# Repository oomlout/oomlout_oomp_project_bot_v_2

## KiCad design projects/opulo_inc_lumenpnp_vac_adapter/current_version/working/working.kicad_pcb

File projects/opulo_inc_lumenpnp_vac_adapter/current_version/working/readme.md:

# lumenpnp
 
## summary 
* id: opulo_inc_lumenpnp_vac_adapter
* user: opulo_inc
* name: lumenpnp
* board: vac_adapter
* repo: https://github.com/opulo-inc/lumenpnp
* src_file_repo_kicad_pcb: pnp/pcb/vac-interposer/vac-adapter.kicad_pcb
* src_file_repo_kicad_pcb_link: https://github.com/opulo-inc/lumenpnp/tree/main/pnp/pcb/vac-interposer/vac-adapter.kicad_pcb
* src_file_repo_kicad_sch: pnp/pcb/vac-interposer/vac-adapter.kicad_sch
* src_file_repo_kicad_sch_link: https://github.com/opulo-inc/lumenpnp/tree/main/pnp/pcb/vac-interposer/vac-adapter.kicad_sch

* src_file_repo_sch: 
* src_file_repo_sch_link: https://github.com/opulo-inc/lumenpnp/tree/main/
* full details link: https://github.com/oomlout/oomlout_oomp_project_bot_v_2/tree/main/projects/opulo_inc_lumenpnp_vac_adapter/current_version/working

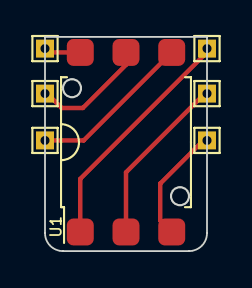
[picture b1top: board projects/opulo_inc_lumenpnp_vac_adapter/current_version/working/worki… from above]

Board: 2 copper layers, 9.0 x 11.9 mm, 7 parts (0 on the bottom side), 6 nets.

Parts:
TP1, TP2, TP3, TP4, TP5, TP6: TestPoint; TestPoint_THTPad_1.0x1.0mm_Drill0.5mm
U1: XGZP; SO-6_7x7mm_P2.54mm

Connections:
unnamed: TP1.1, U1.6 (Vo-)
unnamed: TP2.1, U1.4 (N/C)
unnamed: TP3.1, U1.5 (GND)
unnamed: TP4.1, U1.1 (Vo-)
unnamed: TP5.1, U1.2 (Vs+)
unnamed: TP6.1, U1.3 (Vo+)

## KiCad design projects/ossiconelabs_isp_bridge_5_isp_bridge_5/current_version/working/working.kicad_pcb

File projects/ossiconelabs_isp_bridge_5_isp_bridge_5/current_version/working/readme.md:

# isp_bridge_5
 
## summary 
* id: ossiconelabs_isp_bridge_5_isp_bridge_5
* user: ossiconelabs
* name: isp_bridge_5
* board: isp_bridge_5
* repo: https://github.com/OssiconeLabs/ISP-Bridge-5
* src_file_repo_kicad_pcb: ISP-Bridge-5.kicad_pcb
* src_file_repo_kicad_pcb_link: https://github.com/OssiconeLabs/ISP-Bridge-5/tree/master/ISP-Bridge-5.kicad_pcb

* src_file_repo_sch: ISP-Bridge-5.sch
* src_file_repo_sch_link: https://github.com/OssiconeLabs/ISP-Bridge-5/tree/master/ISP-Bridge-5.sch
* full details link: https://github.com/oomlout/oomlout_oomp_project_bot_v_2/tree/main/projects/ossiconelabs_isp_bridge_5_isp_bridge_5/current_version/working

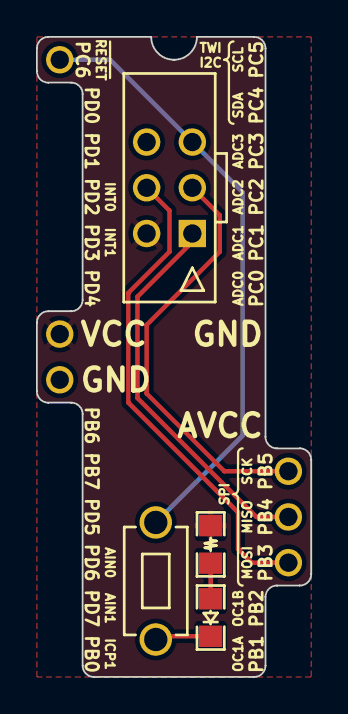
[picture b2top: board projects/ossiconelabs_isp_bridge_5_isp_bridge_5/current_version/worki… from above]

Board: 2 copper layers, 15.2 x 35.6 mm, 6 parts (0 on the bottom side), 7 nets.

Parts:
D1: LED; LED_0805_Symbol
IC1: ATMEGA328-P; Atmel_ATtiny-x8_ATmega-x8
J1: ATMEL_ISP_6PIN; Atmel_ISP_6PIN
R1: 1K; R_0805_Symbol
SW1: SW_PUSH; SW_PUSH_MJTP1250
VAL: REF; Ossicone_Labs_Logo_0.165prop_flipped

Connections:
GND: D1.1, IC1.8, J1.6, SW1.1
unnamed: D1.2, R1.2
unnamed: IC1.1, J1.5, SW1.2
unnamed: IC1.17, J1.4
unnamed: IC1.18, J1.1
unnamed: IC1.19, J1.3
VCC: IC1.7, J1.2, R1.1

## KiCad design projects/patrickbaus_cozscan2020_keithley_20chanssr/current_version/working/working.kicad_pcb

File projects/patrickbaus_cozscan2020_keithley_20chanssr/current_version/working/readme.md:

# cozscan2020
 
## summary 
* id: patrickbaus_cozscan2020_keithley_20chanssr
* user: patrickbaus
* name: cozscan2020
* board: keithley_20chanssr
* repo: https://github.com/PatrickBaus/CozScan2020
* src_file_repo_kicad_pcb: KiCad/Keithley_20ChanSSR/Keithley_20ChanSSR.kicad_pcb
* src_file_repo_kicad_pcb_link: https://github.com/PatrickBaus/CozScan2020/tree/master/KiCad/Keithley_20ChanSSR/Keithley_20ChanSSR.kicad_pcb

* src_file_repo_sch: KiCad/Keithley_20ChanSSR/Keithley_20ChanSSR.sch
* src_file_repo_sch_link: https://github.com/PatrickBaus/CozScan2020/tree/master/KiCad/Keithley_20ChanSSR/Keithley_20ChanSSR.sch
* full details link: https://github.com/oomlout/oomlout_oomp_project_bot_v_2/tree/main/projects/patrickbaus_cozscan2020_keithley_20chanssr/current_version/working

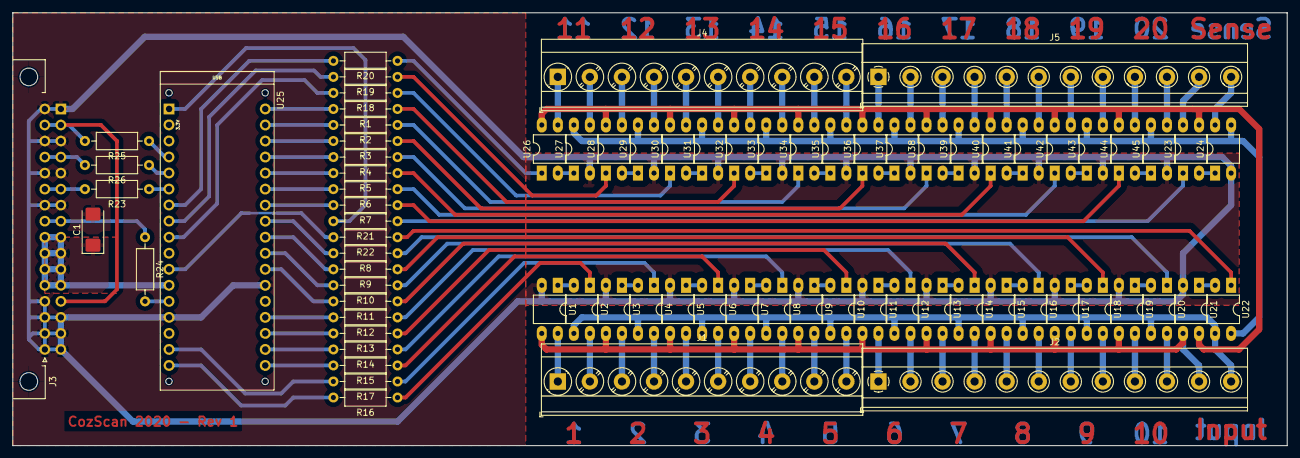
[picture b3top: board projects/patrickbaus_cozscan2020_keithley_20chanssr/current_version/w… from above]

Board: 2 copper layers, 201.9 x 68.6 mm, 77 parts (0 on the bottom side), 122 nets.

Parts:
C1: 10u; CP_EIA-6032-20_AVX-F
J1, J4: Screw_Terminal_01x10; TerminalBlock_Phoenix_MKDS-3-10-5.08_1x10_P5.08mm_Horizontal
J2, J5: Screw_Terminal_01x12; TerminalBlock_Phoenix_MKDS-1,5-12-5.08_1x12_P5.08mm_Horizon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
J3: Conn_02x16_Top_Bottom; DIN41612_B2_2x16_Horizontal
R1, R2, R3, R4, R5, R6, R7, R8, R9, R10, R11, R12, R13, R14, R15, R16, R17, R18, R19, R20, R21, R22, R23, R24, R25, R26: R; R_Axial_DIN0207_L6.3mm_D2.5mm_P10.16mm_Horizontal
U1, U2, U3, U4, U5, U6, U7, U8, U9, U10, U11, U12, U13, U14, U15, U16, U17, U18, U19, U20, U21, U22, U23, U24, U26, U27, U28, U29, U30, U31, U32, U33, U34, U35, U36, U37, U38, U39, U40, U41, U42, U43, U44, U45: TLP3558; DIP-4_W7.62mm_LongPads_coz
U25: Arduino_Micro; Arduino_Micro_Socket_coz

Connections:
+5V: C1.1, J3.9, J3.10, J3.11, J3.12, J3.25, J3.26, J3.27, J3.28, U25.12
/SENSE_LO: J5.11, U23.4
BUSB_2_INPUT: R22.1, U22.1
BUSB_2_SENSE: R21.1, U23.1
CH1: R16.1, U2.1
CH2: R17.1, U4.1
CH3: R15.1, U6.1
CH4: R14.1, U8.1
CH5: R13.1, U10.1
CH6: R12.1, U12.1
CH7: R11.1, U14.1
CH8: R10.1, U16.1
CH9: R9.1, U18.1
CH10: R8.1, U20.1
CH11: R20.1, U26.1
CH12: R19.1, U28.1
CH13: R18.1, U30.1
CH14: R1.1, U32.1
CH15: R2.1, U34.1
CH16: R3.1, U36.1
CH17: R4.1, U38.1
CH18: R5.1, U40.1
CH19: R6.1, U42.1
CH20: R7.1, U44.1
CLK: J3.4, J3.20, R26.2
DATA: J3.2, J3.13, J3.18, R25.2
GND: C1.2, J3.1, J3.3, J3.5, J3.7, J3.14, J3.15, J3.16, J3.17, J3.19, J3.21, J3.23, J3.29, J3.30, J3.31, J3.32, U1.2, U3.2, U5.2, U7.2, U9.2, U11.2, U13.2, U15.2, U17.2, U19.2, U21.2, U24.2, U25.14, U25.23, U27.2, U29.2, U31.2, U33.2, U35.2, U37.2, U39.2, U41.2, U43.2, U45.2
unnamed: J1.1, U1.4
unnamed: J1.2, U2.4
unnamed: J1.3, U3.4
unnamed: J1.4, U4.4
unnamed: J1.5, U5.4
unnamed: J1.6, U6.4
unnamed: J1.7, U7.4
unnamed: J1.8, U8.4
unnamed: J1.9, U9.4
unnamed: J1.10, U10.4
unnamed: J2.1, U11.4
unnamed: J2.2, U12.4
unnamed: J2.3, U13.4
unnamed: J2.4, U14.4
unnamed: J2.5, U15.4
unnamed: J2.6, U16.4
unnamed: J2.7, U17.4
unnamed: J2.8, U18.4
unnamed: J2.9, U19.4
unnamed: J2.10, U20.4
unnamed: J2.11, U1.3, U3.3, U5.3, U7.3, U9.3, U11.3, U13.3, U15.3, U17.3, U19.3, U21.3
unnamed: J2.12, U2.3, U4.3, U6.3, U8.3, U10.3, U12.3, U14.3, U16.3, U18.3, U20.3, U22.3
unnamed: J4.1, U26.3
unnamed: J4.2, U27.3
unnamed: J4.3, U28.3
unnamed: J4.4, U29.3
unnamed: J4.5, U30.3
unnamed: J4.6, U31.3
unnamed: J4.7, U32.3
unnamed: J4.8, U33.3
unnamed: J4.9, U34.3
unnamed: J4.10, U35.3
unnamed: J5.1, U36.3
unnamed: J5.2, U37.3
unnamed: J5.3, U38.3
unnamed: J5.4, U39.3
unnamed: J5.5, U40.3
unnamed: J5.6, U41.3
unnamed: J5.7, U42.3
unnamed: J5.8, U43.3
unnamed: J5.9, U44.3
unnamed: J5.10, U45.3
unnamed: J5.12, U24.4
unnamed: R1.2, U25.34
unnamed: R2.2, U25.33
unnamed: R3.2, U25.32
unnamed: R4.2, U25.31
unnamed: R5.2, U25.30
unnamed: R6.2, U25.29
unnamed: R7.2, U25.28
unnamed: R8.2, U25.27
unnamed: R9.2, U25.26
unnamed: R10.2, U25.25
unnamed: R11.2, U25.24
unnamed: R12.2, U25.21
unnamed: R13.2, U25.20
unnamed: R14.2, U25.19
unnamed: R15.2, U25.18
unnamed: R16.2, U25.17
unnamed: R17.2, U25.16
unnamed: R18.2, U25.9
unnamed: R19.2, U25.8
unnamed: R20.2, U25.7
unnamed: R21.2, U25.1
unnamed: R22.2, U25.11
unnamed: R23.1, U25.6
unnamed: R24.2, U25.13
unnamed: R25.1, U25.4
unnamed: R26.1, U25.5
unnamed: U1.1, U2.2
unnamed: U3.1, U4.2
unnamed: U5.1, U6.2
unnamed: U7.1, U8.2
unnamed: U9.1, U10.2
unnamed: U11.1, U12.2
unnamed: U13.1, U14.2
unnamed: U15.1, U16.2
unnamed: U17.1, U18.2
unnamed: U19.1, U20.2
unnamed: U21.1, U22.2
unnamed: U21.4, U23.3, U26.4, U28.4, U30.4, U32.4, U34.4, U36.4, U38.4, U40.4, U42.4, U44.4
unnamed: U22.4, U24.3, U27.4, U29.4, U31.4, U33.4, U35.4, U37.4, U39.4, U41.4, U43.4, U45.4
unnamed: U23.2, U24.1
unnamed: U26.2, U27.1
unnamed: U28.2, U29.1
unnamed: U30.2, U31.1
unnamed: U32.2, U33.1
unnamed: U34.2, U35.1
unnamed: U36.2, U37.1
unnamed: U38.2, U39.1
unnamed: U40.2, U41.1
unnamed: U42.2, U43.1
unnamed: U44.2, U45.1
RESET: J3.8, J3.24, R24.1
STROBE: J3.6, J3.22, R23.2

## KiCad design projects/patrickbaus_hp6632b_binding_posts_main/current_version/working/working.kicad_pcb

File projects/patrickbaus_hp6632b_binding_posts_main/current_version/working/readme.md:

# hp6632b_binding_posts
 
## summary 
* id: patrickbaus_hp6632b_binding_posts_main
* user: patrickbaus
* name: hp6632b_binding_posts
* board: main
* repo: https://github.com/PatrickBaus/HP6632B_binding_posts
* src_file_repo_kicad_pcb: main.kicad_pcb
* src_file_repo_kicad_pcb_link: https://github.com/PatrickBaus/HP6632B_binding_posts/tree/master/main.kicad_pcb

* src_file_repo_sch: main.sch
* src_file_repo_sch_link: https://github.com/PatrickBaus/HP6632B_binding_posts/tree/master/main.sch
* full details link: https://github.com/oomlout/oomlout_oomp_project_bot_v_2/tree/main/projects/patrickbaus_hp6632b_binding_posts_main/current_version/working

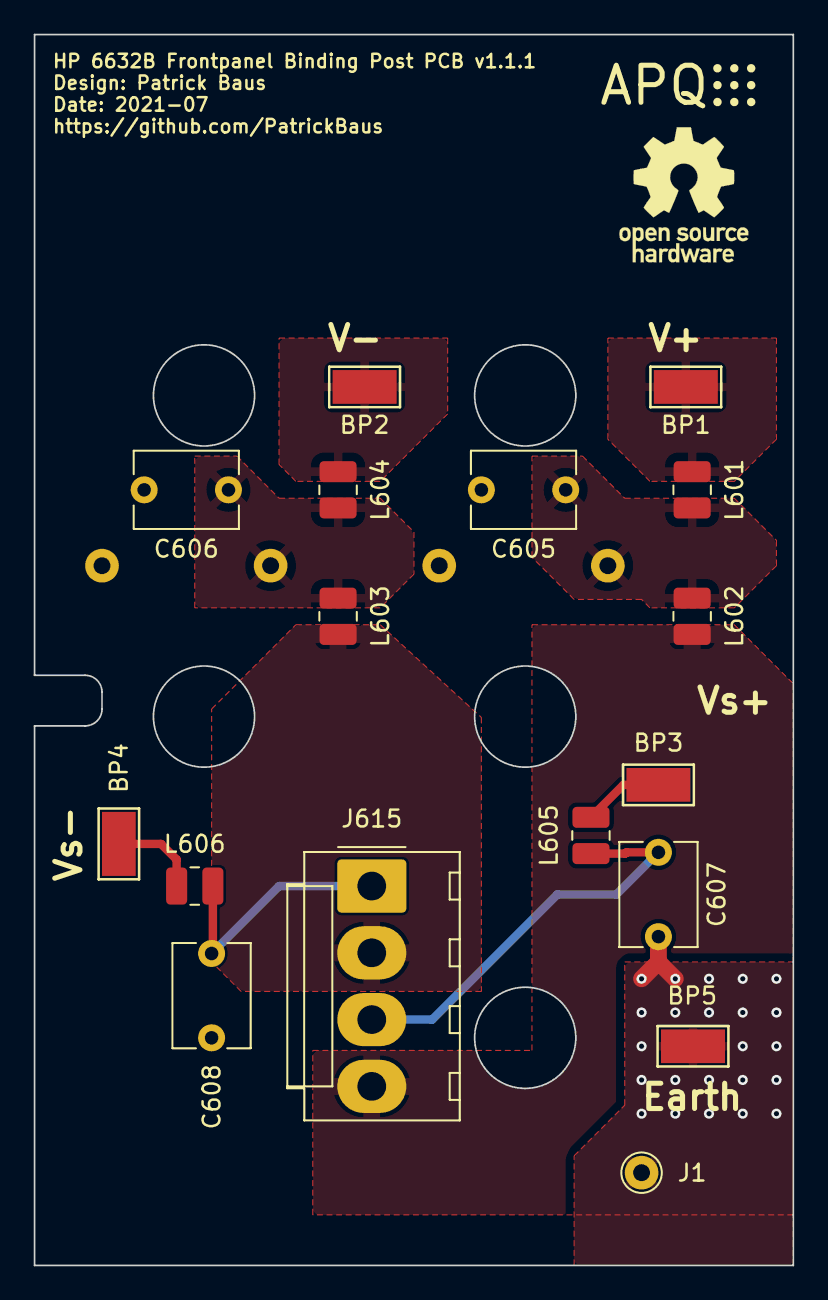
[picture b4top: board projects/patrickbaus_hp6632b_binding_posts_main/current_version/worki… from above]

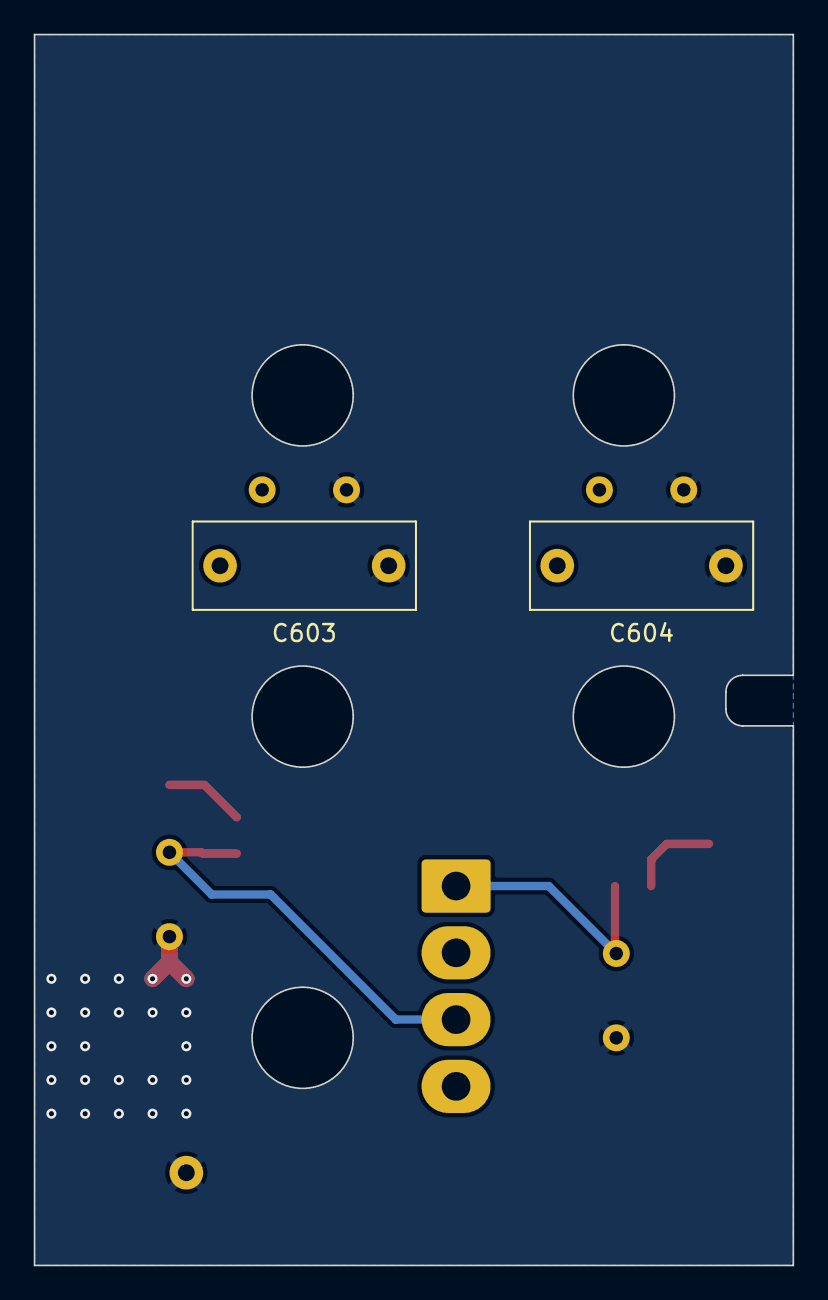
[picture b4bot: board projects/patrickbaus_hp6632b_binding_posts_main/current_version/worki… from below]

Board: 2 copper layers, 45.0 x 73.0 mm, 21 parts (2 on the bottom side), 11 nets.

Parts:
BP1, BP2, BP3, BP4, BP5: Conn_01x01; TestPoint_Keystone_5019_Minature
C603, C604: 4.7n; C_Rect_L13.0mm_W5.0mm_P10.00mm_FKS3_FKP3_MKS4
C605, C606, C607, C608: 220p; C_Disc_D6.0mm_W4.4mm_P5.00mm
J1: Conn_01x01; TestPoint_THTPad_D2.0mm_Drill1.0mm
J615: Conn_01x04_Male; Molex_KK-396_A-41791-0004_1x04_P3.96mm_Vertical
L601, L602, L603, L604, L605, L606: 150n; L_1008_2520Metric
LOGO1: Logo_Open_Hardware_Small; OSHW-Logo_7.5x8mm_SilkScreen
LOGO2: Logo_APQ; APQ-Logo_small

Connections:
/V+: BP1.1, L601.2
/V+_sense: BP3.1, L605.2
/V-: BP2.1, L604.2
/V-_sense: BP4.1, L606.2
Earth: BP5.1, C603.2, C604.1, C605.2, C606.1, C607.2, C608.1, J1.1
unnamed: C603.1, C605.1, L601.1, L602.2
unnamed: C604.2, C606.2, L603.2, L604.1
unnamed: C607.1, J615.3, L605.1
unnamed: C608.2, J615.1, L606.1
unnamed: J615.2, L603.1
unnamed: J615.4, L602.1

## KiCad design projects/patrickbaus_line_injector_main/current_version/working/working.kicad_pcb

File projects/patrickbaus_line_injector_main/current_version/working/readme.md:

# line_injector
 
## summary 
* id: patrickbaus_line_injector_main
* user: patrickbaus
* name: line_injector
* board: main
* repo: https://github.com/PatrickBaus/line_injector
* src_file_repo_kicad_pcb: main.kicad_pcb
* src_file_repo_kicad_pcb_link: https://github.com/PatrickBaus/line_injector/tree/master/main.kicad_pcb
* src_file_repo_kicad_sch: main.kicad_sch
* src_file_repo_kicad_sch_link: https://github.com/PatrickBaus/line_injector/tree/master/main.kicad_sch

* src_file_repo_sch: 
* src_file_repo_sch_link: https://github.com/PatrickBaus/line_injector/tree/master/
* full details link: https://github.com/oomlout/oomlout_oomp_project_bot_v_2/tree/main/projects/patrickbaus_line_injector_main/current_version/working

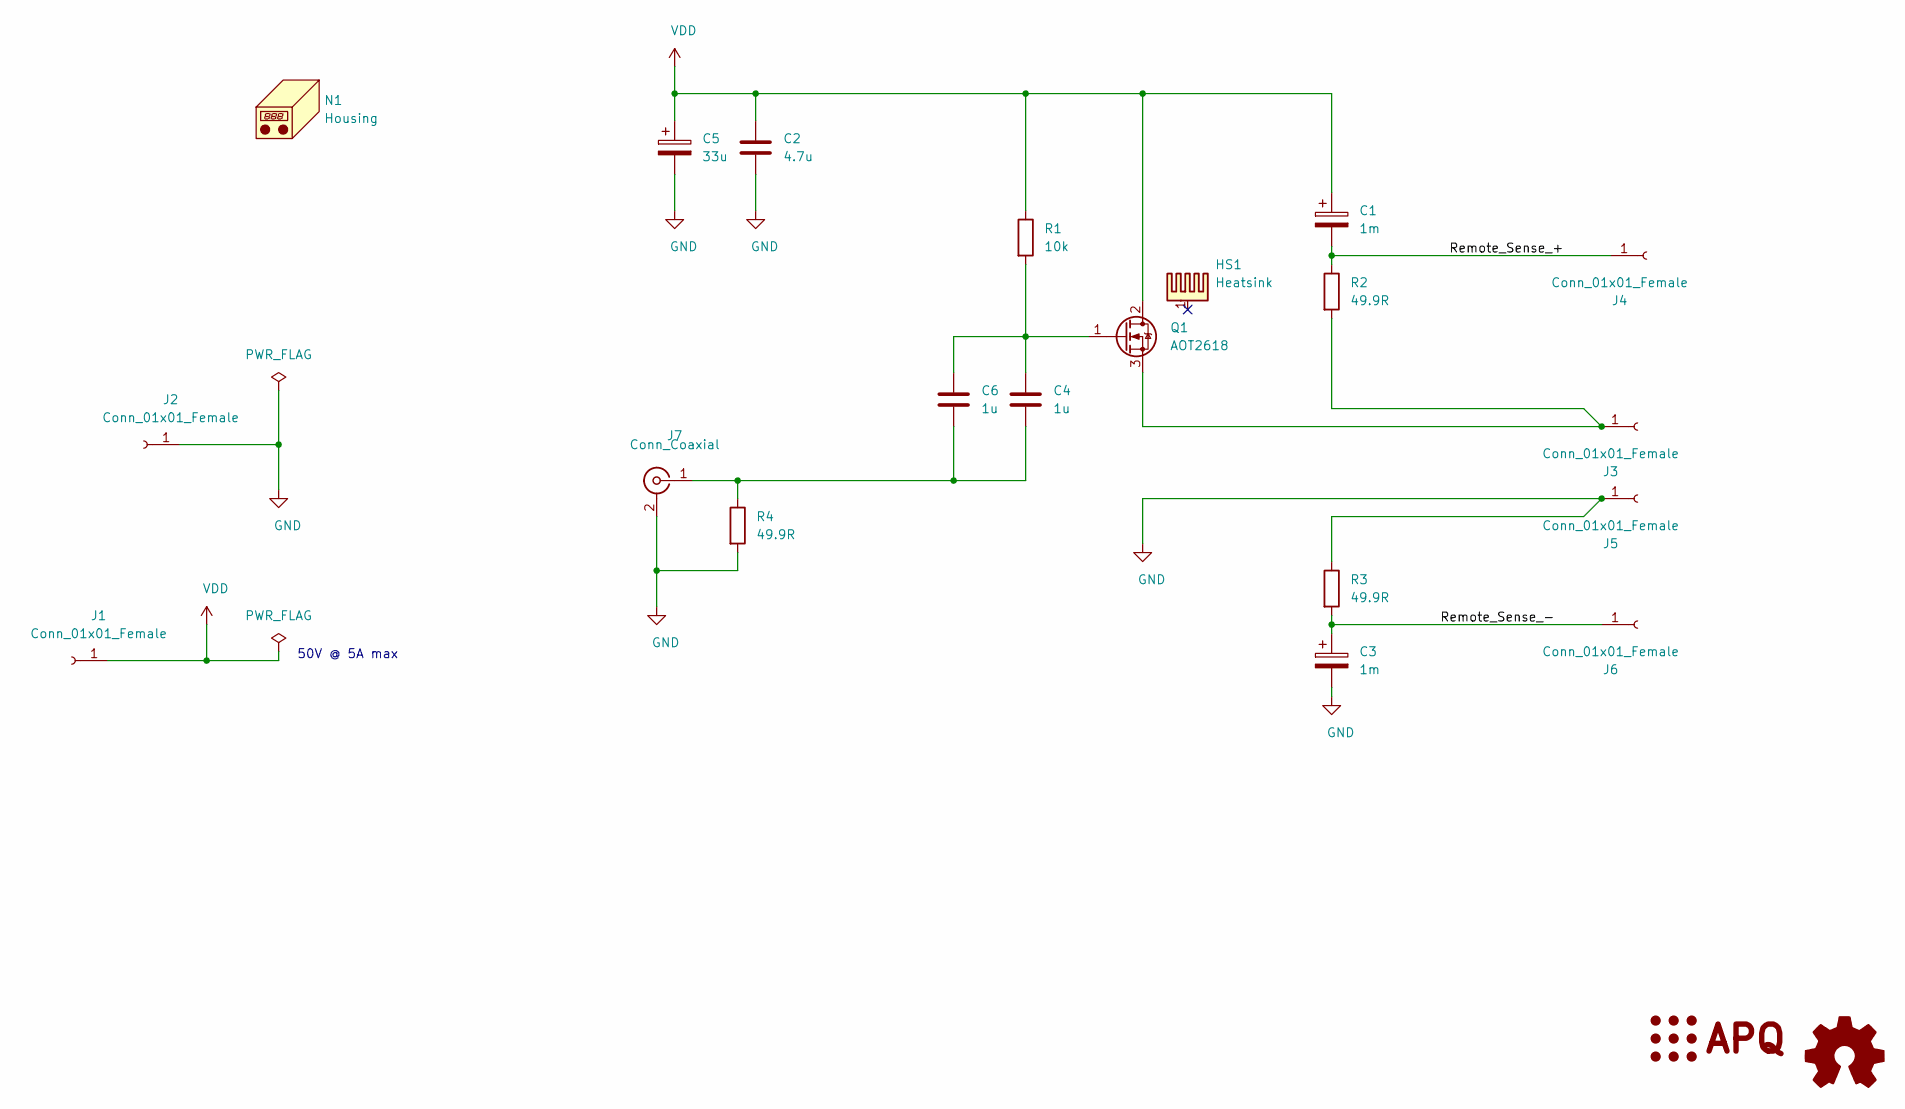
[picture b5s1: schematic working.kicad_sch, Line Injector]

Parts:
C1, C3: 1m; CP_Radial_D18.0mm_P7.50mm
C2: 4.7u; C_1210_3225Metric
C4, C6: 1u; C_1206_3216Metric
C5: 33u; CP_Radial_D10.0mm_P5.00mm
HS1: Heatsink; Heatsink_42x25mm_2xFixation_Ohmite-R-series
J1, J2, J3, J4, J5, J6: Conn_01x01_Female; Schuetzinger_4mm_Jack
J7: Conn_Coaxial; BNC_Amphenol_B6252HB-NPP3G-50_Horizontal
LOGO1: Logo_APQ; APQ-Logo_small
LOGO2: Logo_Open_Hardware_Small; OSHW-Logo_7.5x8mm_SilkScreen
N1: Housing
Q1: AOT2618; TO-220-3_Vertical
R1: 10k; R_0805_2012Metric
R2, R3, R4: 49.9R; R_1206_3216Metric

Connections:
/Remote_Sense_+: C1.2, J4.1, R2.1
/Remote_Sense_-: C3.1, J6.1, R3.2
GND: C2.2, C3.2, C5.2, J2.1, J5.1, J7.2 (Ext), R3.1, R4.2
unnamed: C4.1, C6.1, Q1.1 (G), R1.2
unnamed: C4.2, C6.2, J7.1 (In), R4.1
unnamed: J3.1, Q1.3 (S), R2.2
VDD: C1.1, C2.1, C5.1, J1.1, Q1.2 (D), R1.1

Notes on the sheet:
50V @ 5A max

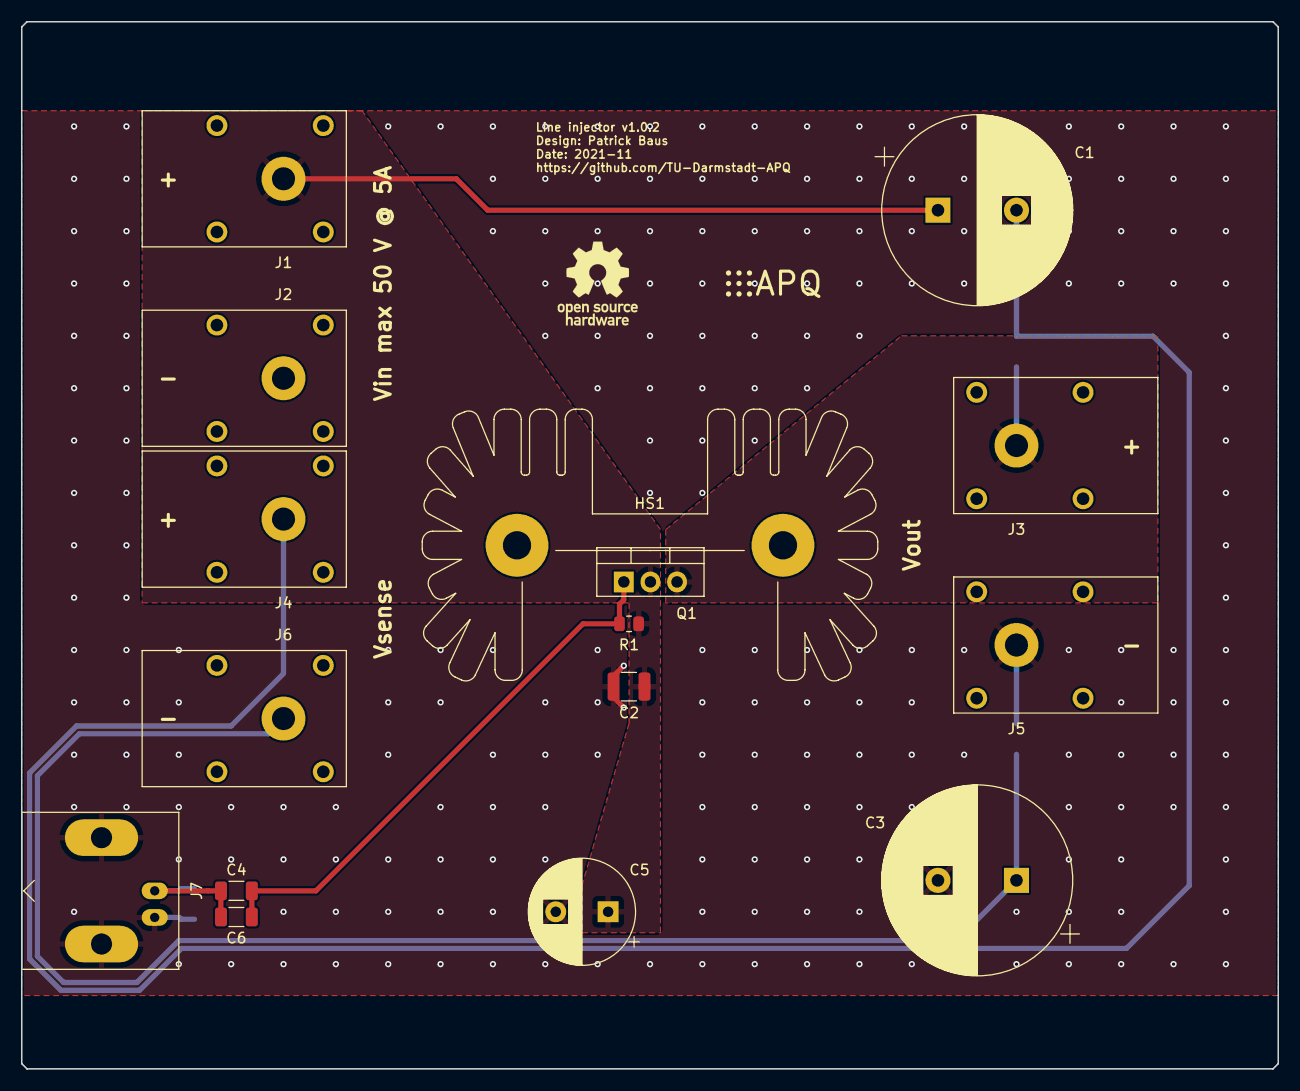
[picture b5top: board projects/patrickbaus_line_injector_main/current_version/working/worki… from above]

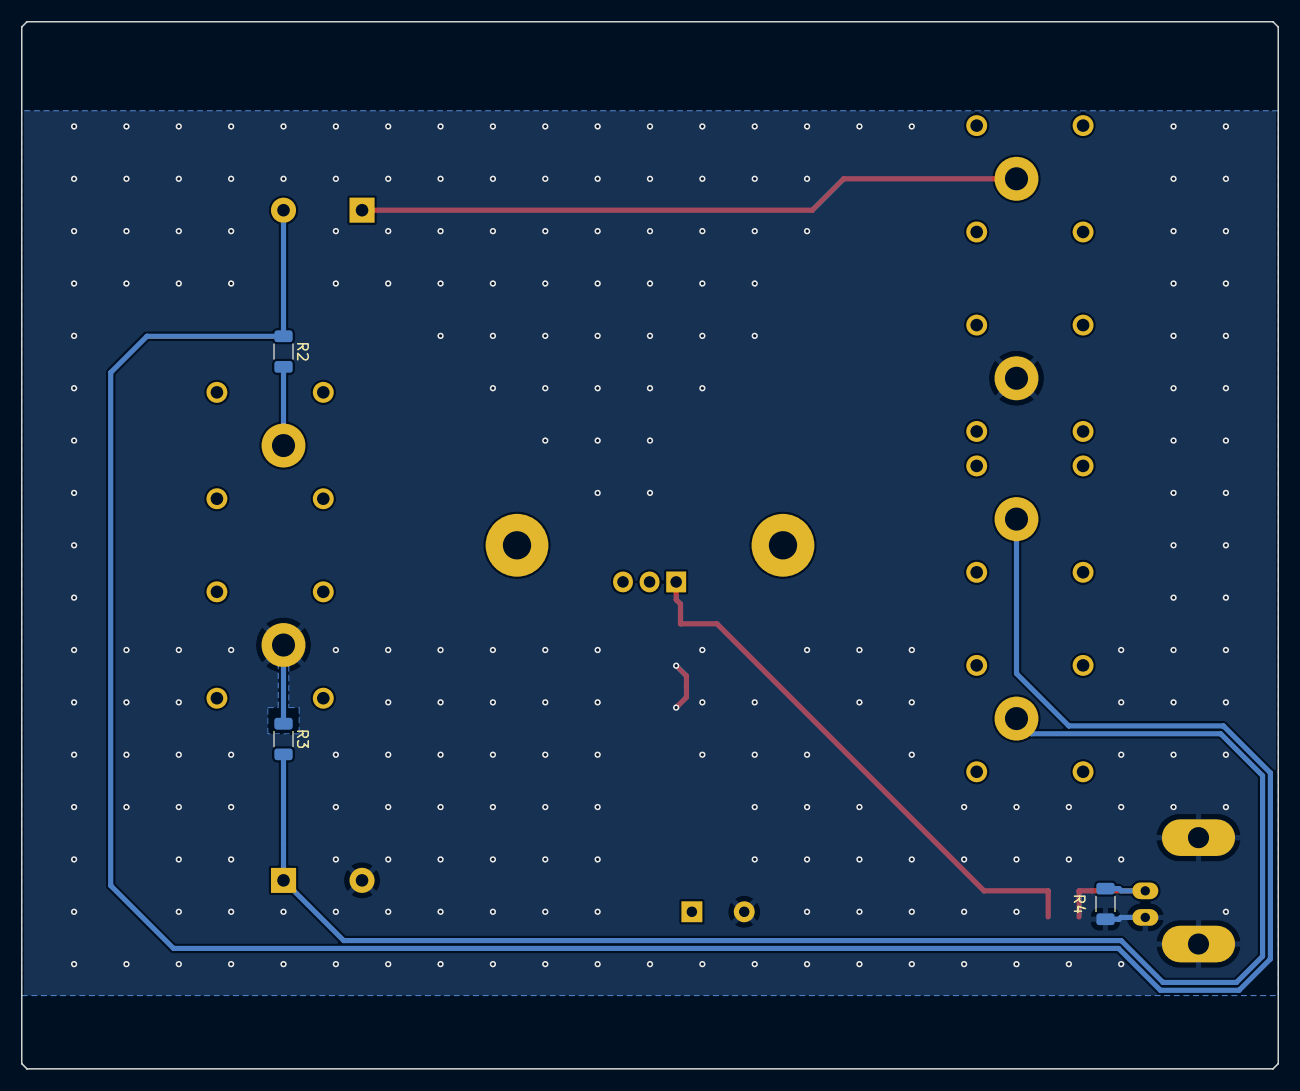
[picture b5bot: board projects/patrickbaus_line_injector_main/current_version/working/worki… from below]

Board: 2 copper layers, 120.0 x 100.0 mm, 21 parts (3 on the bottom side), 7 nets.

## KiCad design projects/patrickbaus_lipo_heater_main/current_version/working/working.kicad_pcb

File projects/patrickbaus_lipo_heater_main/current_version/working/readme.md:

# lipo_heater
 
## summary 
* id: patrickbaus_lipo_heater_main
* user: patrickbaus
* name: lipo_heater
* board: main
* repo: https://github.com/PatrickBaus/LiPo_heater
* src_file_repo_kicad_pcb: main.kicad_pcb
* src_file_repo_kicad_pcb_link: https://github.com/PatrickBaus/LiPo_heater/tree/master/main.kicad_pcb

* src_file_repo_sch: 
* src_file_repo_sch_link: https://github.com/PatrickBaus/LiPo_heater/tree/master/
* full details link: https://github.com/oomlout/oomlout_oomp_project_bot_v_2/tree/main/projects/patrickbaus_lipo_heater_main/current_version/working

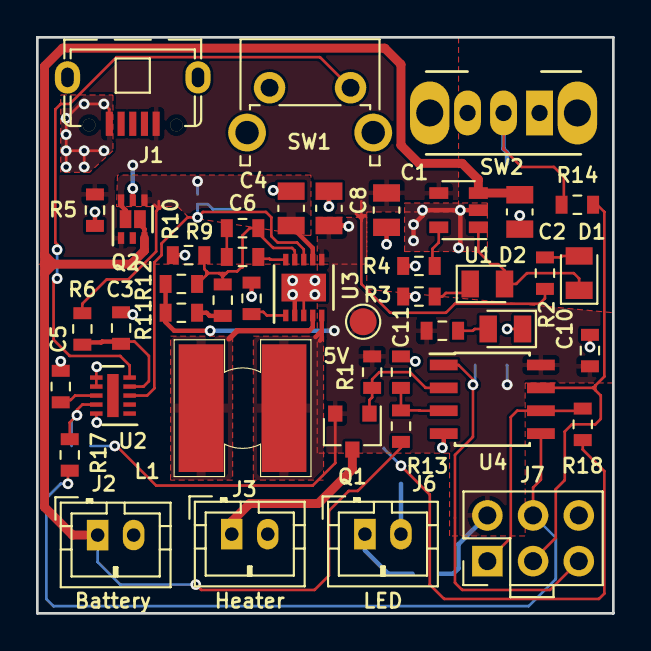
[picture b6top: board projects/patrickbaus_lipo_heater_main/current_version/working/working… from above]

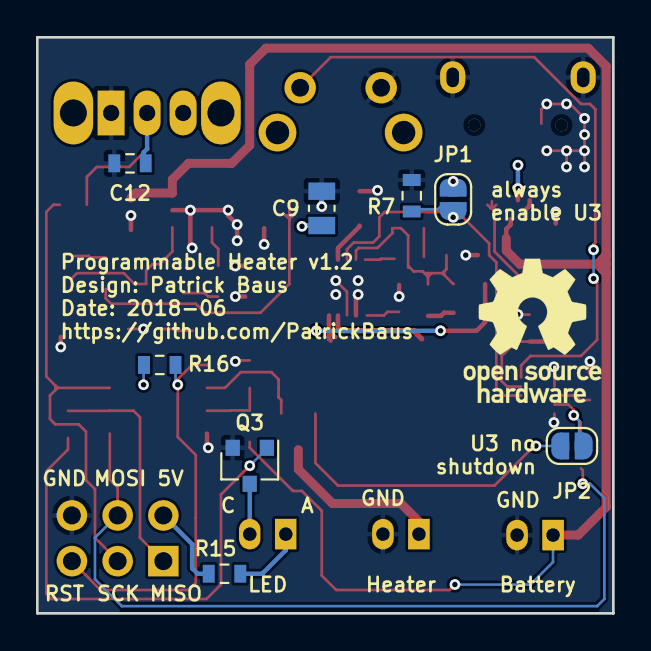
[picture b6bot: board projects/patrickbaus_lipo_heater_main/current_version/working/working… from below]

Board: 2 copper layers, 32.0 x 32.0 mm, 53 parts (9 on the bottom side), 33 nets.

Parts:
C1, C2: 10u; C_0805_2012Metric
C3: 10n; C_0603_1608Metric
C4, C8, C9: 47u; C_0805_2012Metric
C5, C10, C11, C12: 100n; C_0603_1608Metric
C6: 200p; C_0603_1608Metric
C7: 18p; C_0603_1608Metric
D1: Red LED; LED_0805_2012Metric
D2: Green LED; LED_0805_2012Metric
D3: LED; LED_0805_2012Metric
J1: USB_MICRO
J2, J3, J6: Conn_01x02; JST_PH_B2B-PH-K_02x2.00mm_Straight
J7: AVR-ISP-6; PinHeader_2x03_P2.54mm_Vertical
JP1, JP2: SolderJumper_2_Open; SolderJumper-2_P1.3mm_Open_RoundedPad1.0x1.5mm
L1: 22u; Coilcraft_MSS7341
LOGO1: Logo_Open_Hardware_Small; OSHW-Logo_7.5x8mm_SilkScreen
Q1: DMP1045U; SOT-23
Q2: NTLJF3117P; DFN-6-2EP_2x2mm_Pitch0.65mm
Q3: MMBT3904; SOT-23
R1, R16: 10k; R_0603_1608Metric
R2, R15: 470; R_0603_1608Metric
R3, R6, R13, R19: 1k; R_0603_1608Metric
R4: 2k; R_0603_1608Metric
R5, R7: 100k; R_0603_1608Metric
R8: 332k; R_0603_1608Metric
R9: 33k; R_0603_1608Metric
R10: 150k; R_0603_1608Metric
R11: 22.6k; R_0603_1608Metric
R12: 1.1M; R_0603_1608Metric
R14, R17, R18: 4.7k; R_0603_1608Metric
SW1: SW_Push; SW_Tactile_SPST_Angled_PTS645Vx31-2LFS
SW2: SW_SPDT; SW_CuK_OS102011MA1QN1_SPDT_Angled
TP1: Test_Point; TestPoint_Pad_D1.5mm
U1: MCP73831; SOT-23-5
U2: LTC2955-1(DFN); DFN-10-1EP_2x3mm_P0.5mm_EP0.64x2.4mm
U3: LTC3536; DFN-10-1EP_3x3mm_P0.5mm_EP1.55x2.48mm
U4: ATtiny13-20SSU; SOIC-8_3.9x4.9mm_P1.27mm

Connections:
/BAT+: C2.1, J2.1, Q2.3, Q2.8, R13.2, U1.3
/Microcontroller/MISO: J7.1, R18.2, U4.6
/Microcontroller/MOSI: J7.4, R17.2, U4.5
/Microcontroller/RST: J7.5, R16.2, U4.1
/Microcontroller/SCK: J7.3, R14.2, U4.7
/Microcontroller/~enable_heater: Q1.1, R1.2, U4.2
/Power Supply/DC/DC boost converter/Vsup: C4.1, JP1.1, Q2.4, Q2.6, Q2.7, R6.1, U3.7
/Power Supply/V+5: C8.1, C9.1, C10.1, J7.2, JP2.1, Q1.2, R1.1, R11.1, R12.1, R15.1, R16.1, R19.1, TP1.1, U3.6, U4.8
/Power Supply/VUSB: C1.1, J1.1, Q2.1, Q2.5, R2.2, R5.1, U1.4
/Power Supply/~Kill_power: JP2.2, R17.1, U2.9
GND: C1.2, C2.2, C3.2, C4.2, C5.2, C8.2, C9.2, C10.2, C11.2, C12.2, D3.1, J1.5, J1.6, J2.2, J3.2, J7.6, Q3.2, R3.1, R4.1, R5.2, R7.2, R8.2, R10.2, SW1.1, SW2.1, U1.2, U2.6, U2.7, U2.10, U3.2, U3.3, U3.11, U4.4
unnamed: C3.1, R6.2, U2.4
unnamed: C5.1, U2.8
unnamed: C6.1, R9.1
unnamed: C6.2, C7.2, R10.1, R12.2, U3.9
unnamed: C7.1, R11.2
unnamed: C11.1, R13.1, U4.3
unnamed: C12.1, R14.1, SW2.2
unnamed: D1.1, D2.2, U1.1
unnamed: D1.2, R2.1
unnamed: D2.1, R3.2
unnamed: D3.2, R19.2
unnamed: J3.1, Q1.3
unnamed: J6.1, R15.2
unnamed: J6.2, Q3.3
unnamed: JP1.2, R7.1, U2.3, U3.8
unnamed: L1.1, U3.4
unnamed: L1.2, U3.5
unnamed: Q3.1, R18.1
unnamed: R4.2, U1.5
unnamed: R8.1, U3.1
unnamed: R9.2, U3.10
unnamed: SW1.2, U2.5

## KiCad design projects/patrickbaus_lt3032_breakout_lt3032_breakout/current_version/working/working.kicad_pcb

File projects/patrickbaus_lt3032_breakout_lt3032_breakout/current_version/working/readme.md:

# lt3032_breakout
 
## summary 
* id: patrickbaus_lt3032_breakout_lt3032_breakout
* user: patrickbaus
* name: lt3032_breakout
* board: lt3032_breakout
* repo: https://github.com/PatrickBaus/LT3032_breakout
* src_file_repo_kicad_pcb: LT3032-breakout.kicad_pcb
* src_file_repo_kicad_pcb_link: https://github.com/PatrickBaus/LT3032_breakout/tree/master/LT3032-breakout.kicad_pcb

* src_file_repo_sch: LT3032-breakout.sch
* src_file_repo_sch_link: https://github.com/PatrickBaus/LT3032_breakout/tree/master/LT3032-breakout.sch
* full details link: https://github.com/oomlout/oomlout_oomp_project_bot_v_2/tree/main/projects/patrickbaus_lt3032_breakout_lt3032_breakout/current_version/working

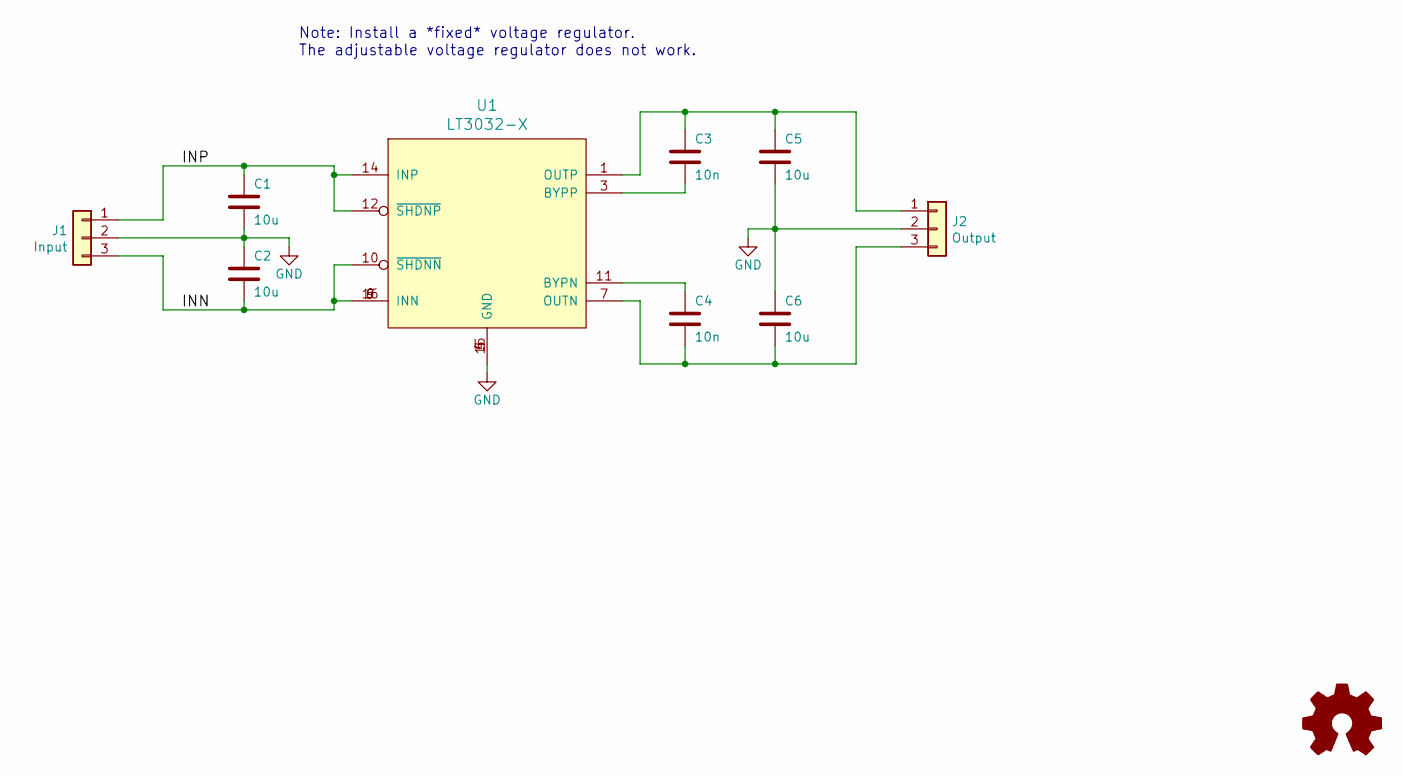
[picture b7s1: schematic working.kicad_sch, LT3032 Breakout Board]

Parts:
C1, C2, C5, C6: 10u; C_1210_3225Metric
C3, C4: 10n; C_0603_1608Metric
J1: Input; PinHeader_1x03_P2.54mm_Vertical
J2: Output; PinHeader_1x03_P2.54mm_Vertical
U1: LT3032-X; Linear_DE14MA

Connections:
/INN: C2.1, J1.3, U1.6 (INN), U1.9, U1.10 (~SHDNN), U1.16
/INP: C1.2, J1.1, U1.12 (~SHDNP), U1.14 (INP)
GND: C1.1, C2.2, C5.1, C6.2, J1.2, J2.2, U1.4, U1.5, U1.15 (GND)
unnamed: C3.1, U1.3 (BYPP)
unnamed: C3.2, C5.2, J2.1, U1.1 (OUTP)
unnamed: C4.1, C6.1, J2.3, U1.7 (OUTN)
unnamed: C4.2, U1.11 (BYPN)

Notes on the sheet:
Note: Install a *fixed* voltage regulator. The adjustable voltage regulator does not work.

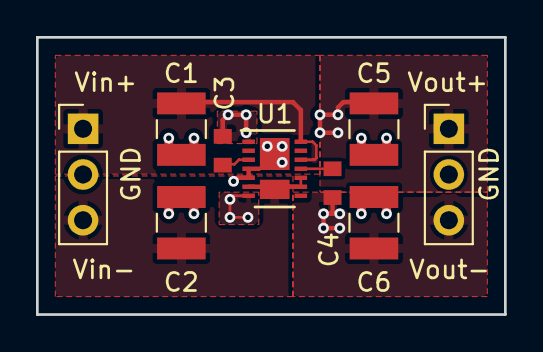
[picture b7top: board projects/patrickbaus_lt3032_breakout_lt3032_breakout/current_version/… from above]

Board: 2 copper layers, 26.0 x 15.4 mm, 9 parts (0 on the bottom side), 7 nets.

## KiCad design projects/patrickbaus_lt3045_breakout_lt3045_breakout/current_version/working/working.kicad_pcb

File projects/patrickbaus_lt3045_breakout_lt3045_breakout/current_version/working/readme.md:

# lt3045_breakout
 
## summary 
* id: patrickbaus_lt3045_breakout_lt3045_breakout
* user: patrickbaus
* name: lt3045_breakout
* board: lt3045_breakout
* repo: https://github.com/PatrickBaus/LT3045_breakout
* src_file_repo_kicad_pcb: LT3045_breakout.kicad_pcb
* src_file_repo_kicad_pcb_link: https://github.com/PatrickBaus/LT3045_breakout/tree/master/LT3045_breakout.kicad_pcb

* src_file_repo_sch: LT3045_breakout.sch
* src_file_repo_sch_link: https://github.com/PatrickBaus/LT3045_breakout/tree/master/LT3045_breakout.sch
* full details link: https://github.com/oomlout/oomlout_oomp_project_bot_v_2/tree/main/projects/patrickbaus_lt3045_breakout_lt3045_breakout/current_version/working

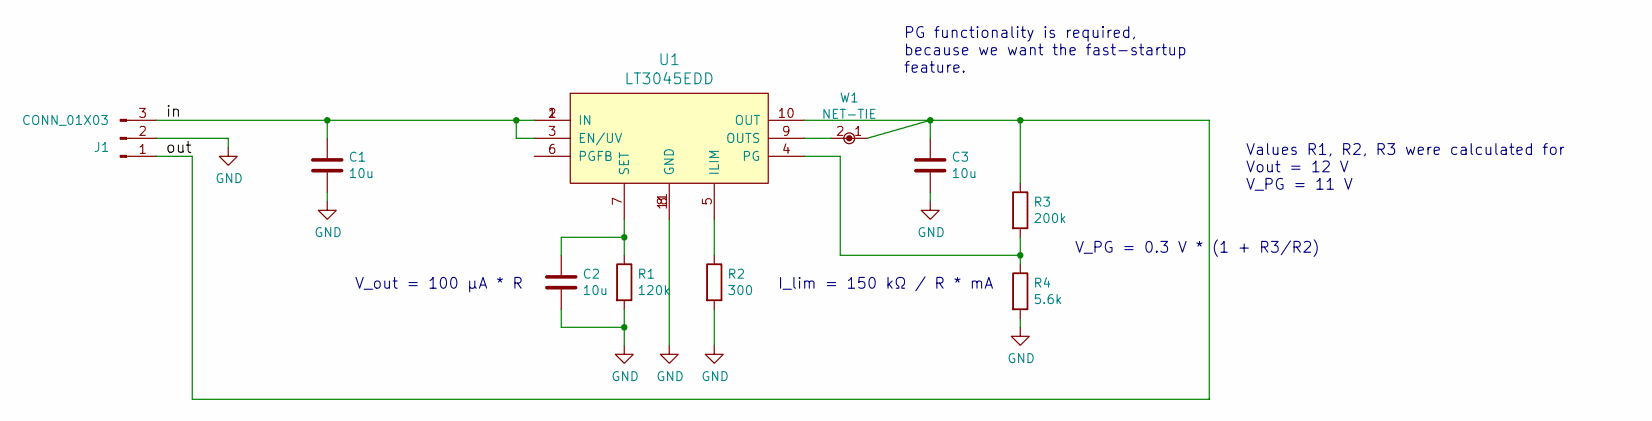
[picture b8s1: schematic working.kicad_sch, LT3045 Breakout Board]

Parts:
C1, C2, C3: 10u; C_0603
J1: CONN_01X03; Pin_Header_Angled_1x03_Pitch2.54mm
R1: 120k; R_0603
R2: 300; R_0603
R3: 200k; R_0402
R4: 5.6k; R_0402
U1: LT3045EDD; DFN-10-1EP_3x3mm_Pitch0.5mm
W1: NET-TIE; NET-TIE-0.15mm

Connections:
/in: C1.1, J1.3, U1.1 (IN), U1.2 (IN), U1.3 (EN/UV)
/out: C3.1, J1.1, R3.1, U1.10 (OUT), W1.1
GND: C1.2, C2.2, C3.2, J1.2, R1.2, R2.2, R4.2, U1.8 (GND), U1.11
unnamed: C2.1, R1.1, U1.7 (SET)
unnamed: R2.1, U1.5 (ILIM)
unnamed: R3.2, R4.1, U1.4 (PG)
unnamed: U1.9 (OUTS), W1.2

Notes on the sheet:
Values R1, R2, R3 were calculated for Vout = 12 V V_PG = 11 V
V_PG = 0.3 V * (1 + R3/R2)
V_out = 100 µA * R
I_lim = 150 kΩ / R * mA
PG functionality is required, because we want the fast-startup feature.

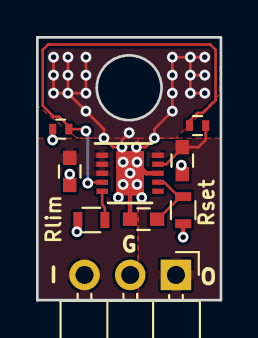
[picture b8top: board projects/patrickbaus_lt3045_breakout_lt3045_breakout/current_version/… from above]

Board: 2 copper layers, 10.2 x 14.6 mm, 10 parts (0 on the bottom side), 7 nets.

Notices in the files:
projects/patrickbaus_hp6632b_binding_posts_main/current_version/working/working.kicad_pcb:
Copyright (©) 2020, Patrick Baus
Licensed under CERN OHL v.1.2
projects/patrickbaus_line_injector_main/current_version/working/working.kicad_pcb:
Copyright (©) 2021, Patrick Baus
projects/patrickbaus_lt3032_breakout_lt3032_breakout/current_version/working/working.kicad_sch:
Copyright (©) 2017, Patrick Baus
